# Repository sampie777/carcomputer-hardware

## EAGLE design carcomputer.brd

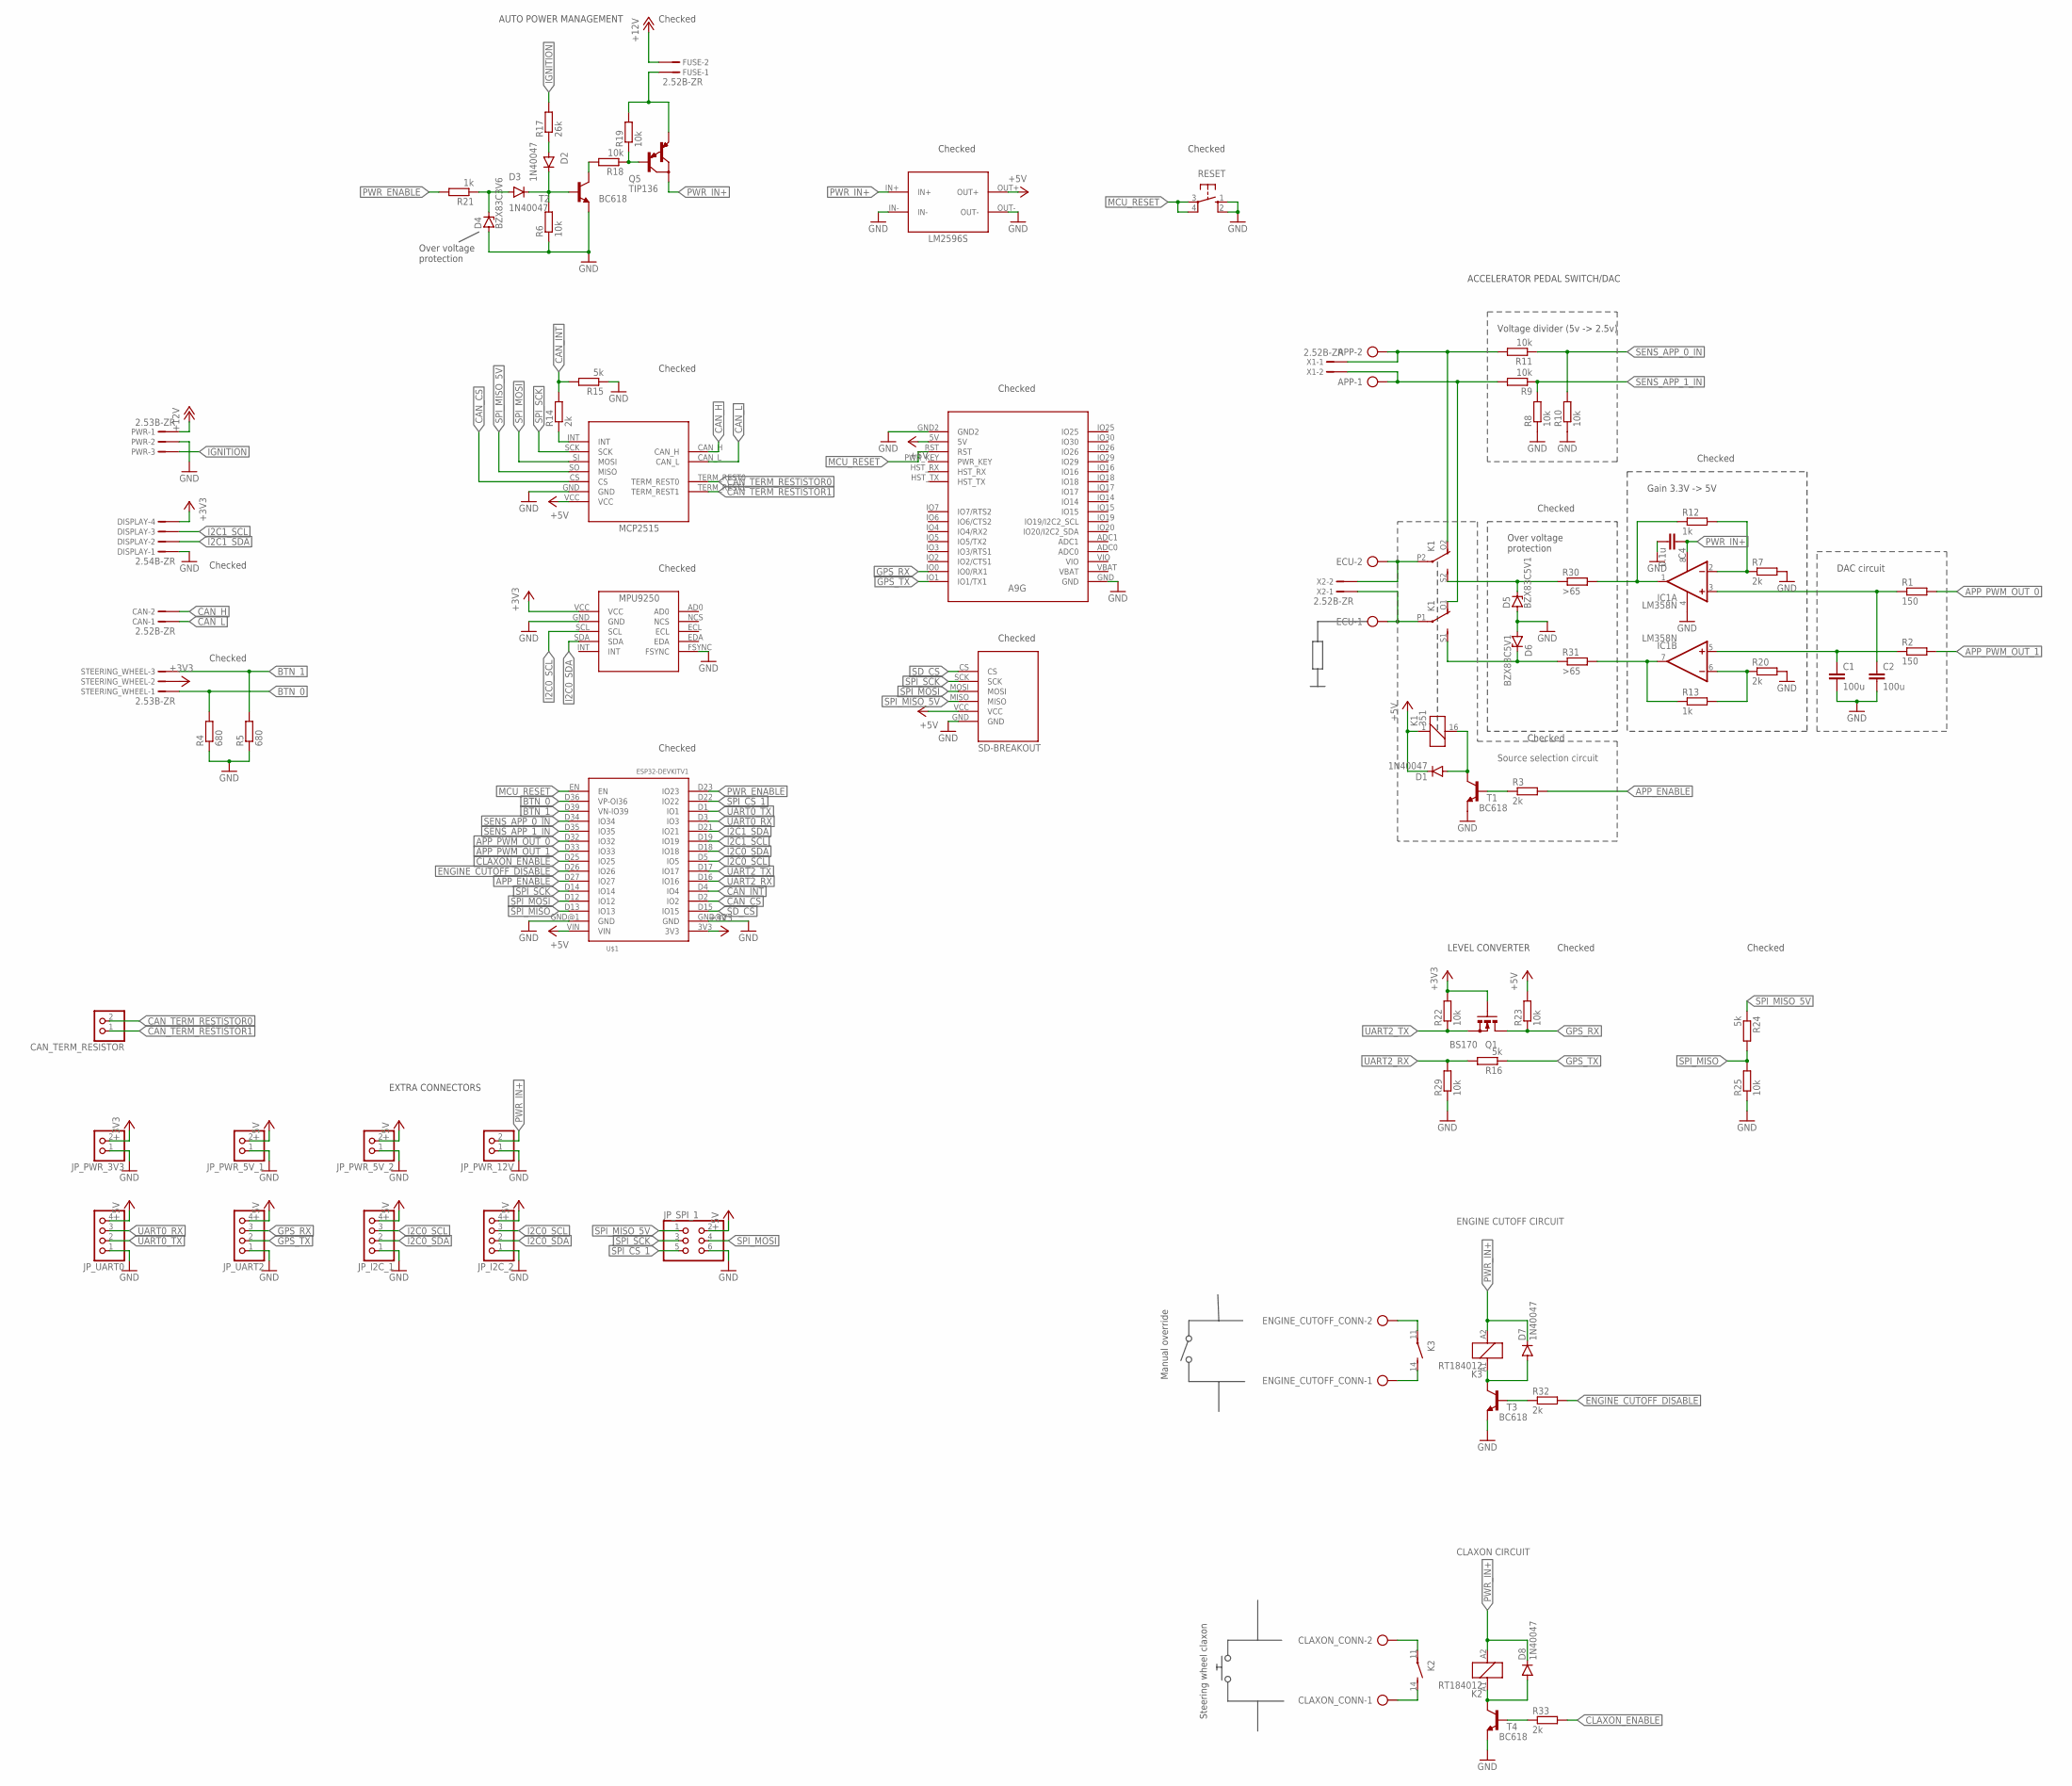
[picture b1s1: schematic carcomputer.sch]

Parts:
APP: AK300/2
C1, C2: 100u; C025-050X050
C4: 0.1u; C025-050X050
CAN: 2.52B-ZR; B2B-ZR2.5
CAN_TERM_RESISTOR: PINHD-1X2; 1X02
CLAXON_CONN: AK300/2
D1, D2, D3, D7, D8: 1N40047; DO41-7.6
D4: BZX83C3V6; DO41Z7.6
D5, D6: BZX83C5V1; DO41Z7.6
DISPLAY: 2.54B-ZR; B4B-ZR2.5
ECU: AK300/2
ENGINE_CUTOFF_CONN: AK300/2
FUSE: 2.52B-ZR; B2B-ZR2.5
IC1: LM358N; DIL08
JP_I2C_1, JP_I2C_2: PINHD-1X4; 1X04
JP_PWR_3V3, JP_PWR_5V_1, JP_PWR_5V_2, JP_PWR_12V: PINHD-1X2; 1X02
JP_SPI_1: PINHD-2X3; 2X03
JP_UART0, JP_UART2: PINHD-1X4; 1X04
K1: 351
K2, K3: RT184012; RT-N/O12A3.5
PWR: 2.53B-ZR; B3B-ZR2.5
Q1: BS170; SOT54E
Q5: TIP136; TO220
R1, R2: 150; 0309/10
R3, R7, R20: 2k; 0207/7
R4, R5: 680; 0207/7
R6, R8, R10, R18, R19, R22, R23, R25, R29: 10k; 0207/7
R9, R11: 10k; 0309/10
R12, R13: 1k; 0207/7
R14, R32, R33: 2k; 0309/10
R15, R16, R24: 5k; 0207/7
R17: 26k; 0207/7
R21: 1k; 0309/10
R30, R31: >65; 0207/7
RESET: 10-XX; B3F-10XX
STEERING_WHEEL: 2.53B-ZR; B3B-ZR2.5
T1, T2, T3, T4: BC618; TO92-EBC
U$1: ESP32DEVKITV1; ESP32-DEVKITV1
U$2: MCP2515_DEVBOARDINVERTED; MCP2515_DEVBOARD_INVERTED
U$3: MPU9250_BREAKOUT
U$4: LM2596S
U$5: HKD-MICRO-SD-BREAKOUTH; HKD-MICRO-SD-BREAKOUT
U$6: A9G
X1, X2: 2.52B-ZR; B2B-ZR2.5

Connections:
+3V3: DISPLAY.4, JP_PWR_3V3.2, Q1.G, R22.2, STEERING_WHEEL.2, U$1.3V3, U$3.VCC
+5V: D1.C, JP_I2C_1.4, JP_I2C_2.4, JP_PWR_5V_1.2, JP_PWR_5V_2.2, JP_SPI_1.2, JP_UART0.4, JP_UART2.4, K1.1, R23.2, U$1.VIN, U$2.VCC, U$4.OUT+, U$5.VCC, U$6.5V
+12V: FUSE.2, PWR.1
APP_0_IN: APP.2, K1.O2 (O), R11.2, X1.1
APP_1_IN: APP.1, K1.O1 (O), R9.2, X1.2
APP_ENABLE: R3.2, U$1.D27 (IO27)
APP_PWM_OUT_0: R1.2, U$1.D32 (IO32)
APP_PWM_OUT_1: R2.2, U$1.D33 (IO33)
BTN_0: R4.2, STEERING_WHEEL.1, U$1.D36 (VP-OI36)
BTN_1: R5.2, STEERING_WHEEL.3, U$1.D39 (VN-IO39)
CAN_CS: U$1.D2 (IO2), U$2.CS
CAN_H: CAN.2, U$2.CAN_H
CAN_INT: R14.2, R15.2, U$1.D4 (IO4)
CAN_L: CAN.1, U$2.CAN_L
CAN_TERM_RESTISTOR0: CAN_TERM_RESISTOR.2, U$2.TERM_REST0
CAN_TERM_RESTISTOR1: CAN_TERM_RESISTOR.1, U$2.TERM_REST1
CLAXON_ENABLE: R33.2, U$1.D25 (IO25)
ENGINE_CUTOFF_DISABLE: R32.2, U$1.D26 (IO26)
GND: C1.2, C2.2, C4.2, D4.A, D5.A, D6.A, DISPLAY.1, IC1.4 (V-), JP_I2C_1.1, JP_I2C_2.1, JP_PWR_3V3.1, JP_PWR_5V_1.1, JP_PWR_5V_2.1, JP_PWR_12V.1, JP_SPI_1.6, JP_UART0.1, JP_UART2.1, PWR.2, R4.1, R5.1, R6.1, R7.2, R8.1, R10.1, R15.1, R20.2, R25.1, R29.1, RESET.1 (S), RESET.2 (S1), T1.E, T2.E, T3.E, T4.E, U$1.GND@1 (GND), U$1.GND@2 (GND), U$2.GND, U$3.FSYNC, U$3.GND, U$4.IN-, U$4.OUT-, U$5.GND, U$6.GND, U$6.GND2
GPS_RX: JP_UART2.3, Q1.D, R23.1, U$6.IO0 (IO0/RX1)
GPS_TX: JP_UART2.2, R16.1, U$6.IO1 (IO1/TX1)
I2C0_SCL: JP_I2C_1.3, JP_I2C_2.3, U$1.D5 (IO5), U$3.SCL
I2C0_SDA: JP_I2C_1.2, JP_I2C_2.2, U$1.D18 (IO18), U$3.SDA
I2C1_SCL: DISPLAY.3, U$1.D19 (IO19)
I2C1_SDA: DISPLAY.2, U$1.D21 (IO21)
IGNITION: PWR.3, R17.2
MCU_RESET: RESET.3, RESET.4 (P1), U$1.EN, U$6.RST
unnamed: D1.A, K1.16 (2), T1.C
unnamed: R3.1, T1.B
unnamed: D6.C, K1.S1 (S), R31.1
unnamed: IC1.1 (OUT), R12.1, R30.2
unnamed: D2.C, D3.C, R6.2, T2.B
unnamed: ECU.2, K1.P2, X2.2
unnamed: ECU.1, K1.P1, X2.1
unnamed: C2.1, IC1.3 (+IN), R1.1
unnamed: C1.1, IC1.5 (+IN), R2.1
unnamed: R14.1, U$2.INT
unnamed: D3.A, D4.C, R21.1
unnamed: D2.A, R17.1
unnamed: IC1.2 (-IN), R7.1, R12.2
unnamed: Q5.1 (B), R18.1, R19.1
unnamed: R18.2, T2.C
unnamed: IC1.6 (-IN), R13.2, R20.1
unnamed: D5.C, K1.S2 (S), R30.1
unnamed: IC1.7 (OUT), R13.1, R31.2
unnamed: ENGINE_CUTOFF_CONN.2, K3.11
unnamed: ENGINE_CUTOFF_CONN.1, K3.14 (S)
unnamed: FUSE.1, Q5.3 (E), R19.2
unnamed: D7.A, K3.A1 (1), T3.C
unnamed: D8.A, K2.A1 (1), T4.C
unnamed: R33.1, T4.B
unnamed: R32.1, T3.B
unnamed: CLAXON_CONN.2, K2.11
unnamed: CLAXON_CONN.1, K2.14 (S)
PWR_ENABLE: R21.2, U$1.D23 (IO23)
PWR_IN+: C4.1, D7.C, D8.C, IC1.8 (V+), JP_PWR_12V.2, K2.A2 (2), K3.A2 (2), Q5.2 (C), U$4.IN+
SD_CS: U$1.D15 (IO15), U$5.CS
SENS_APP_0_IN: R10.2, R11.1, U$1.D34 (IO34)
SENS_APP_1_IN: R8.2, R9.1, U$1.D35 (IO35)
SPI_CS_1: JP_SPI_1.5, U$1.D22 (IO22)
SPI_MISO: R24.2, R25.2, U$1.D13 (IO13)
SPI_MISO_5V: JP_SPI_1.1, R24.1, U$2.SO (MISO), U$5.MISO
SPI_MOSI: JP_SPI_1.4, U$1.D12 (IO12), U$2.SI (MOSI), U$5.MOSI
SPI_SCK: JP_SPI_1.3, U$1.D14 (IO14), U$2.SCK, U$5.SCK
UART0_RX: JP_UART0.3, U$1.D3 (IO3)
UART0_TX: JP_UART0.2, U$1.D1 (IO1)
UART2_RX: R16.2, R29.2, U$1.D16 (IO16)
UART2_TX: Q1.S, R22.1, U$1.D17 (IO17)

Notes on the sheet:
Voltage divider (5v -> 2.5v)
DAC circuit
Source selection circuit
Over voltage protection
AUTO POWER MANAGEMENT
ACCELERATOR PEDAL SWITCH/DAC
EXTRA CONNECTORS
Gain 3.3V -> 5V
Checked
LEVEL CONVERTER
ENGINE CUTOFF CIRCUIT
Manual override
CLAXON CIRCUIT
Steering wheel claxon

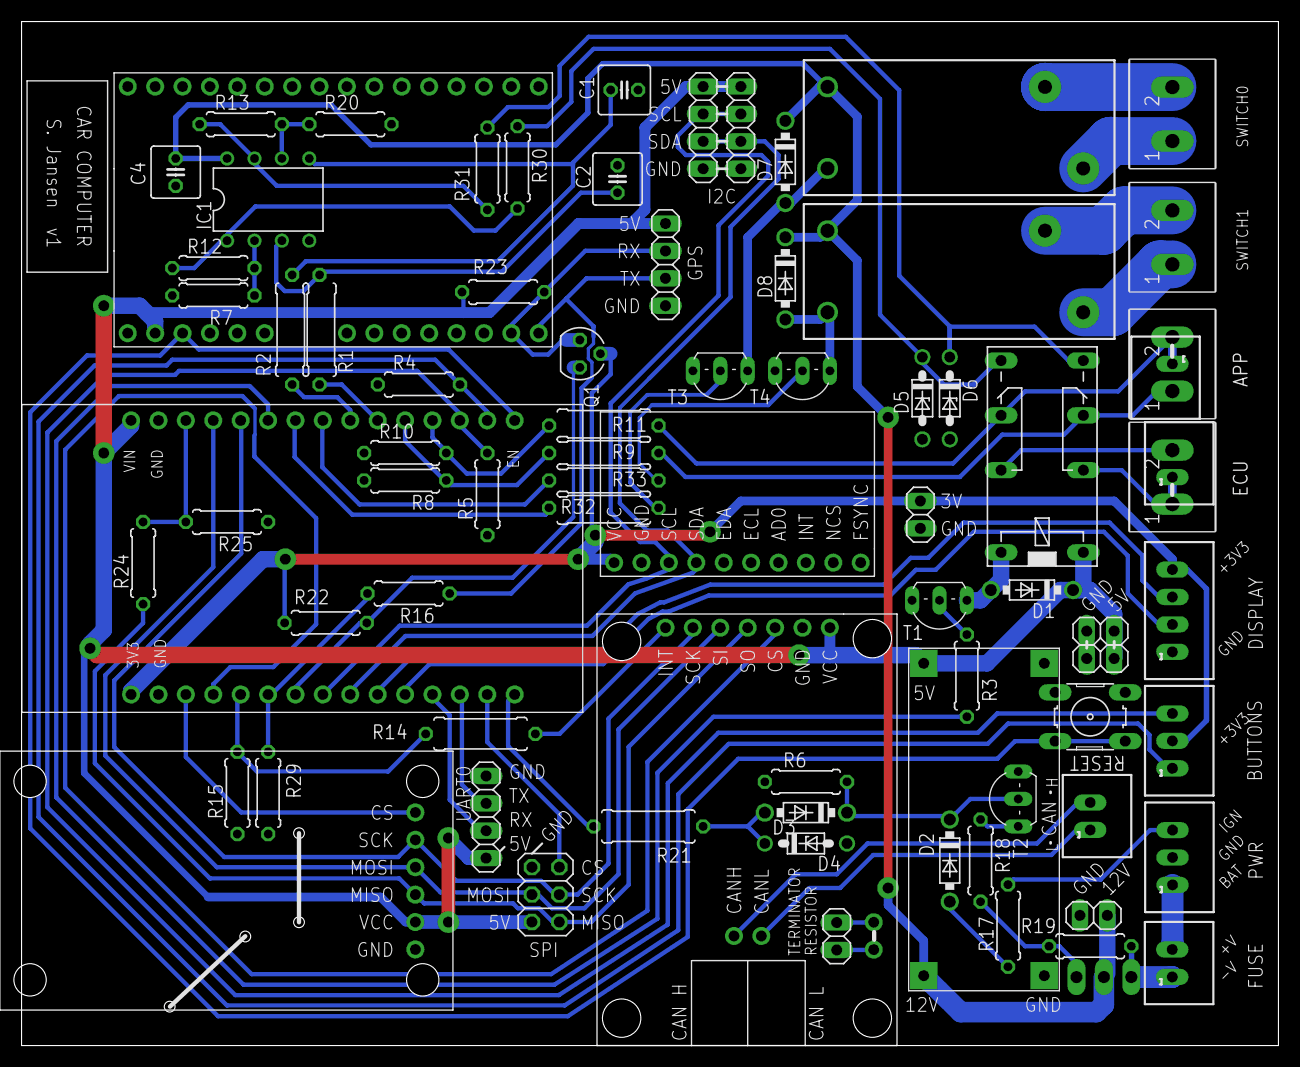
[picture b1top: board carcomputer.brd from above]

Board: 2 copper layers, 116.5 x 94.9 mm, 79 parts (1 on the bottom side), 68 nets.

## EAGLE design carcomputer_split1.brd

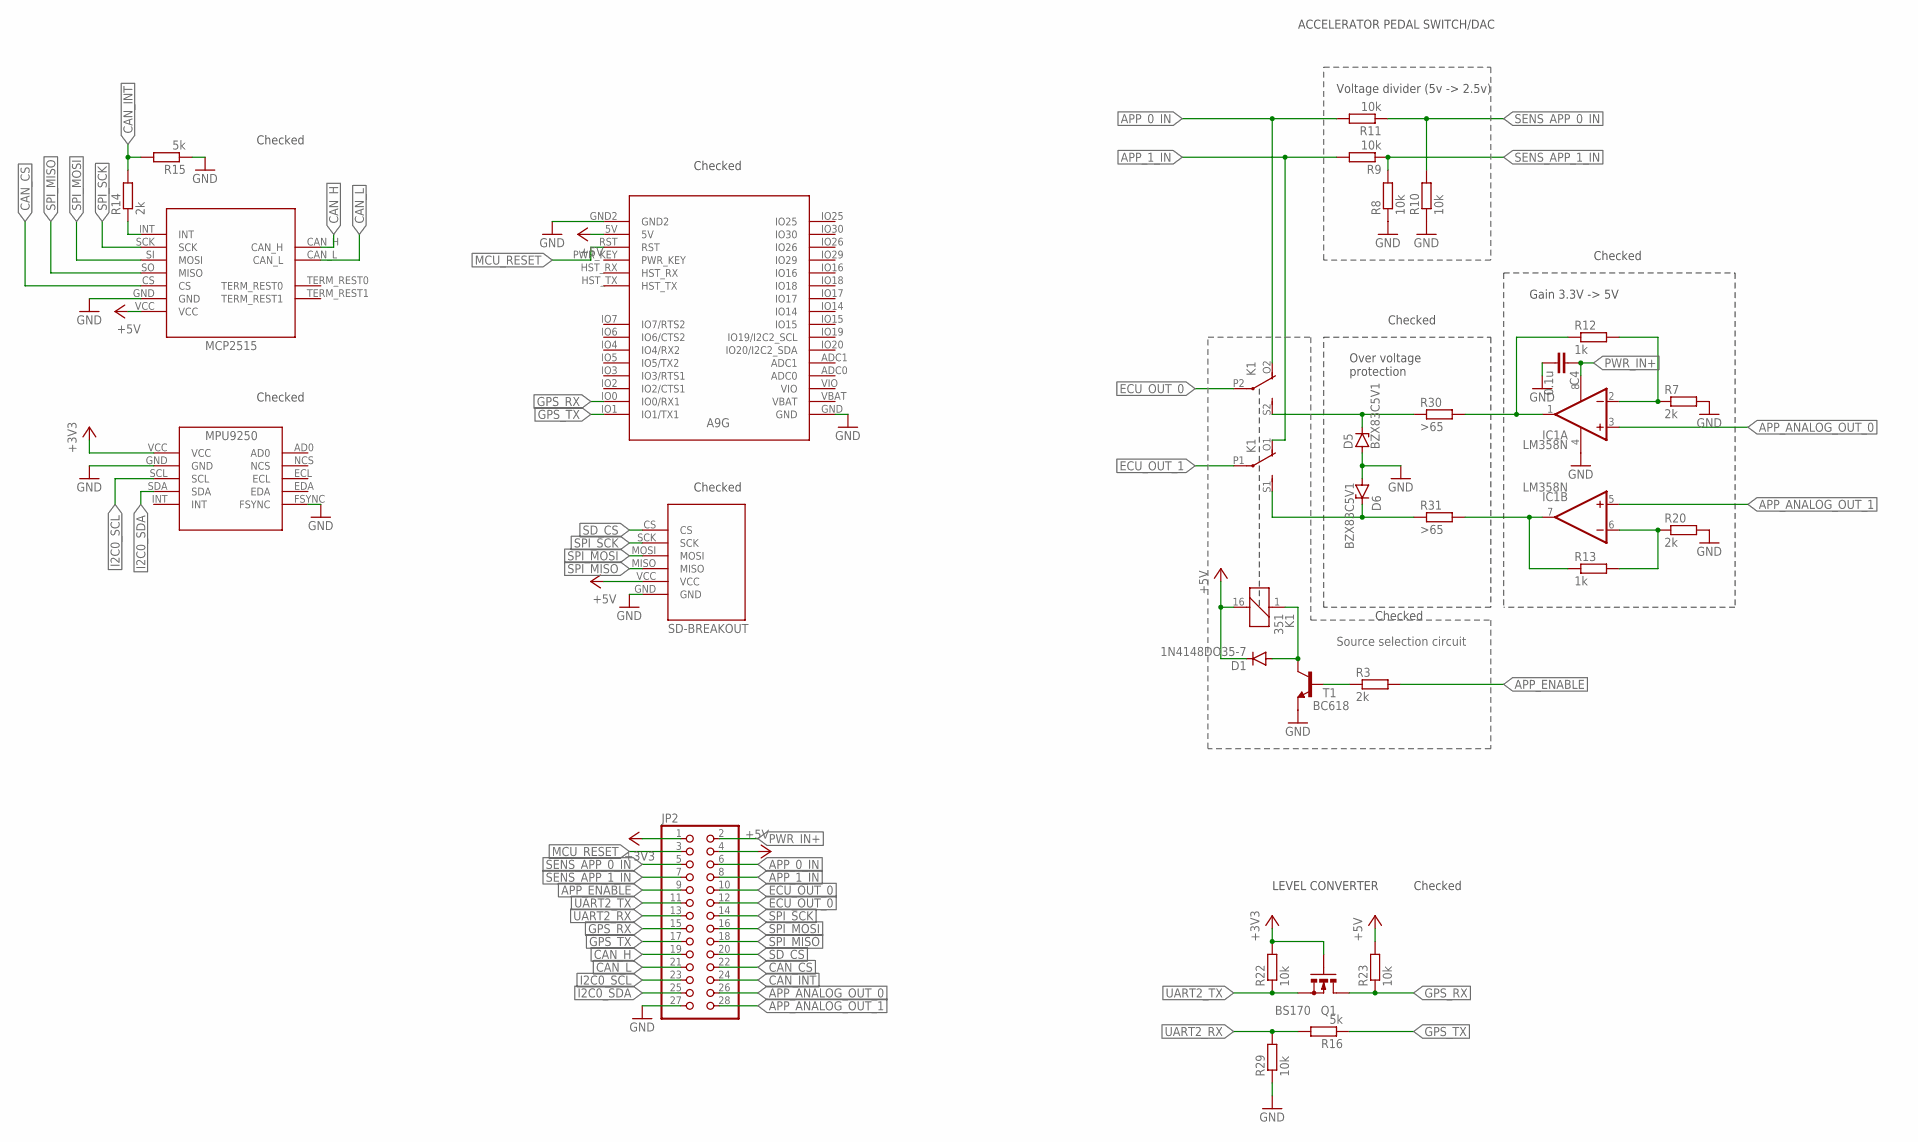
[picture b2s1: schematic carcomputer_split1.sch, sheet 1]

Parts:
C4: 0.1u; C025-050X050
D1: 1N4148DO35-7; DO35-7
D5, D6: BZX83C5V1; DO41Z10
IC1: LM358N; DIL08
JP2: PINHD-2X14; 2X14
K1: 351
Q1: BS170; SOT54E
R3, R7, R14, R20: 2k; 0207/7
R8, R9, R10, R11, R22, R23, R29: 10k; 0207/7
R12, R13: 1k; 0207/7
R15, R16: 5k; 0207/7
R30, R31: >65; 0207/7
T1: BC618; TO92-EBC
U$2: MCP2515_DEVBOARDINVERTED; MCP2515_DEVBOARD_INVERTED
U$3: MPU9250_BREAKOUT
U$5: HKD-MICRO-SD-BREAKOUT
U$6: A9G

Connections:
+3V3: JP2.1, Q1.G, R22.2, U$3.VCC; also elsewhere on the board
+5V: D1.C, JP2.4, K1.16 (2), R23.2, U$2.VCC, U$5.VCC, U$6.5V; also elsewhere on the board
APP_0_IN: JP2.6, K1.O2 (O), R11.2; also elsewhere on the board
APP_1_IN: JP2.8, K1.O1 (O), R9.2; also elsewhere on the board
APP_ANALOG_OUT_0: IC1.3 (+IN), JP2.26; also elsewhere on the board
APP_ANALOG_OUT_1: IC1.5 (+IN), JP2.28; also elsewhere on the board
APP_ENABLE: JP2.9, R3.2; also elsewhere on the board
CAN_CS: JP2.22, U$2.CS; also elsewhere on the board
CAN_H: JP2.19, U$2.CAN_H; also elsewhere on the board
CAN_INT: JP2.24, R14.2, R15.2; also elsewhere on the board
CAN_L: JP2.21, U$2.CAN_L; also elsewhere on the board
ECU_OUT_0: JP2.10, JP2.12, K1.P2; also elsewhere on the board
ECU_OUT_1: K1.P1; also elsewhere on the board
GND: C4.2, D5.A, D6.A, IC1.4 (V-), JP2.27, R7.2, R8.1, R10.1, R15.1, R20.2, R29.1, T1.E, U$2.GND, U$3.FSYNC, U$3.GND, U$5.GND, U$6.GND, U$6.GND2; also elsewhere on the board
GPS_RX: JP2.15, Q1.D, R23.1, U$6.IO0 (IO0/RX1); also elsewhere on the board
GPS_TX: JP2.17, R16.1, U$6.IO1 (IO1/TX1); also elsewhere on the board
I2C0_SCL: JP2.23, U$3.SCL; also elsewhere on the board
I2C0_SDA: JP2.25, U$3.SDA; also elsewhere on the board
MCU_RESET: JP2.3, U$6.RST; also elsewhere on the board
unnamed: D1.A, K1.1, T1.C
unnamed: R3.1, T1.B
unnamed: D6.C, K1.S1 (S), R31.1
unnamed: IC1.1 (OUT), R12.1, R30.2
unnamed: R14.1, U$2.INT
unnamed: IC1.2 (-IN), R7.1, R12.2
unnamed: IC1.6 (-IN), R13.2, R20.1
unnamed: D5.C, K1.S2 (S), R30.1
unnamed: IC1.7 (OUT), R13.1, R31.2
PWR_IN+: C4.1, IC1.8 (V+), JP2.2; also elsewhere on the board
SD_CS: JP2.20, U$5.CS; also elsewhere on the board
SENS_APP_0_IN: JP2.5, R10.2, R11.1; also elsewhere on the board
SENS_APP_1_IN: JP2.7, R8.2, R9.1; also elsewhere on the board
SPI_MISO: JP2.18, U$2.SO (MISO), U$5.MISO; also elsewhere on the board
SPI_MOSI: JP2.16, U$2.SI (MOSI), U$5.MOSI; also elsewhere on the board
SPI_SCK: JP2.14, U$2.SCK, U$5.SCK; also elsewhere on the board
UART2_RX: JP2.13, R16.2, R29.2; also elsewhere on the board
UART2_TX: JP2.11, Q1.S, R22.1; also elsewhere on the board

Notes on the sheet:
Voltage divider (5v -> 2.5v)
Source selection circuit
ACCELERATOR PEDAL SWITCH/DAC
Gain 3.3V -> 5V
Over voltage protection
Checked
LEVEL CONVERTER

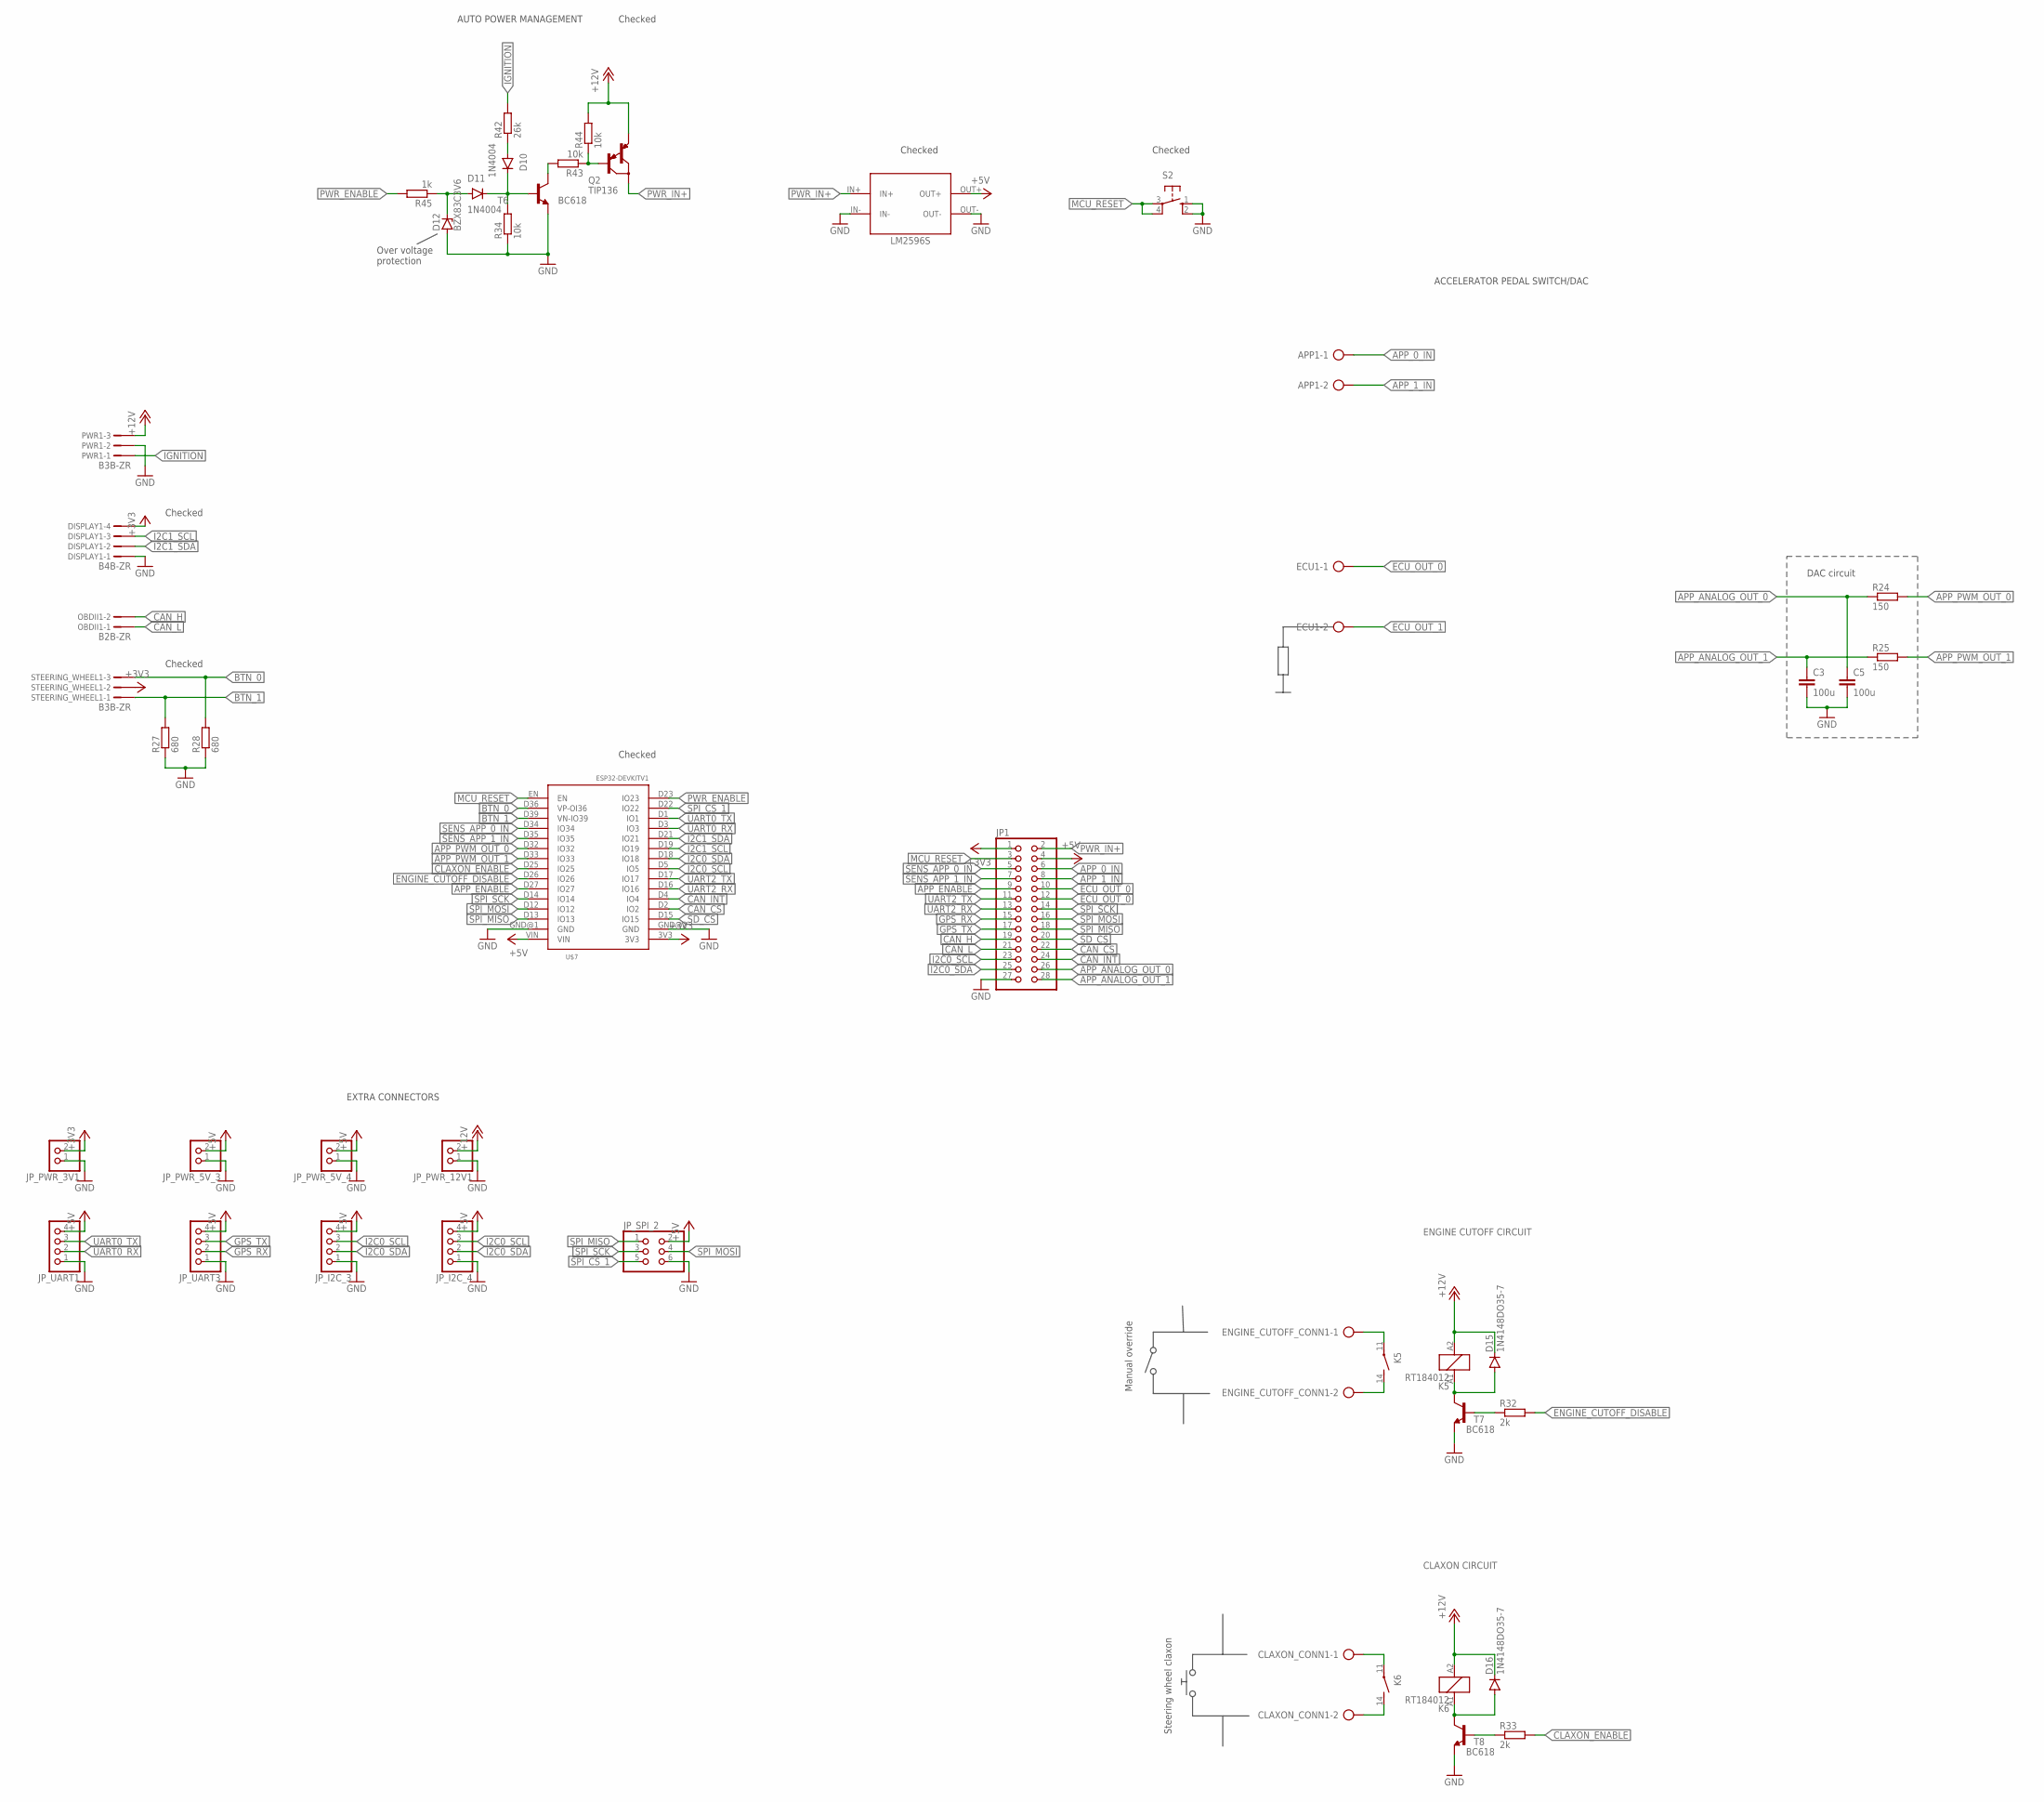
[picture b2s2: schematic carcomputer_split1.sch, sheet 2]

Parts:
APP1: AK300/2
C3, C5: 100u; C025-050X050
CLAXON_CONN1: AK300/2
D10, D11: 1N4004; DO41-10
D12: BZX83C3V6; DO41Z10
D15, D16: 1N4148DO35-7; DO35-7
DISPLAY1: B4B-ZR
ECU1: AK300/2
ENGINE_CUTOFF_CONN1: AK300/2
JP1: PINHD-2X14; 2X14
JP_I2C_3, JP_I2C_4: PINHD-1X4; 1X04
JP_PWR_3V1, JP_PWR_5V_3, JP_PWR_5V_4, JP_PWR_12V1: PINHD-1X2; 1X02
JP_SPI_2: PINHD-2X3; 2X03
JP_UART1, JP_UART3: PINHD-1X4; 1X04
K5, K6: RT184012; RT-N/O12A3.5
OBDII1: B2B-ZR
PWR1: B3B-ZR
Q2: TIP136; TO220
R24, R25: 150; 0207/7
R27, R28: 680; 0207/7
R32, R33: 2k; 0207/7
R34, R43, R44: 10k; 0207/7
R42: 26k; 0207/7
R45: 1k; 0207/7
S2: 10-XX; B3F-10XX
STEERING_WHEEL1: B3B-ZR
T6, T7, T8: BC618; TO92-EBC
U$7: ESP32DEVKITV1; ESP32-DEVKITV1
U$10: LM2596S

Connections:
+3V3: DISPLAY1.4, JP1.1, JP_PWR_3V1.2, STEERING_WHEEL1.2, U$7.3V3; also elsewhere on the board
+5V: JP1.4, JP_I2C_3.4, JP_I2C_4.4, JP_PWR_5V_3.2, JP_PWR_5V_4.2, JP_SPI_2.2, JP_UART1.4, JP_UART3.4, U$7.VIN, U$10.OUT+; also elsewhere on the board
+12V: D15.C, D16.C, JP_PWR_12V1.2, K5.A2 (2), K6.A2 (2), PWR1.3, Q2.3 (E), R44.2
APP_0_IN: APP1.1, JP1.6; also elsewhere on the board
APP_1_IN: APP1.2, JP1.8; also elsewhere on the board
APP_ANALOG_OUT_0: C5.1, JP1.26, R24.1; also elsewhere on the board
APP_ANALOG_OUT_1: C3.1, JP1.28, R25.1; also elsewhere on the board
APP_ENABLE: JP1.9, U$7.D27 (IO27); also elsewhere on the board
APP_PWM_OUT_0: R24.2, U$7.D32 (IO32)
APP_PWM_OUT_1: R25.2, U$7.D33 (IO33)
BTN_0: R28.2, STEERING_WHEEL1.3, U$7.D36 (VP-OI36)
BTN_1: R27.2, STEERING_WHEEL1.1, U$7.D39 (VN-IO39)
CAN_CS: JP1.22, U$7.D2 (IO2); also elsewhere on the board
CAN_H: JP1.19, OBDII1.2; also elsewhere on the board
CAN_INT: JP1.24, U$7.D4 (IO4); also elsewhere on the board
CAN_L: JP1.21, OBDII1.1; also elsewhere on the board
CLAXON_ENABLE: R33.2, U$7.D25 (IO25)
ECU_OUT_0: ECU1.1, JP1.10, JP1.12; also elsewhere on the board
ECU_OUT_1: ECU1.2; also elsewhere on the board
ENGINE_CUTOFF_DISABLE: R32.2, U$7.D26 (IO26)
GND: C3.2, C5.2, D12.A, DISPLAY1.1, JP1.27, JP_I2C_3.1, JP_I2C_4.1, JP_PWR_3V1.1, JP_PWR_5V_3.1, JP_PWR_5V_4.1, JP_PWR_12V1.1, JP_SPI_2.6, JP_UART1.1, JP_UART3.1, PWR1.2, R27.1, R28.1, R34.1, S2.1 (S), S2.2 (S1), T6.E, T7.E, T8.E, U$7.GND@1 (GND), U$7.GND@2 (GND), U$10.IN-, U$10.OUT-; also elsewhere on the board
GPS_RX: JP1.15, JP_UART3.2; also elsewhere on the board
GPS_TX: JP1.17, JP_UART3.3; also elsewhere on the board
I2C0_SCL: JP1.23, JP_I2C_3.3, JP_I2C_4.3, U$7.D5 (IO5); also elsewhere on the board
I2C0_SDA: JP1.25, JP_I2C_3.2, JP_I2C_4.2, U$7.D18 (IO18); also elsewhere on the board
I2C1_SCL: DISPLAY1.3, U$7.D19 (IO19)
I2C1_SDA: DISPLAY1.2, U$7.D21 (IO21)
IGNITION: PWR1.1, R42.2
MCU_RESET: JP1.3, S2.3, S2.4 (P1), U$7.EN; also elsewhere on the board
unnamed: D10.C, D11.C, R34.2, T6.B
unnamed: D10.A, R42.1
unnamed: Q2.1 (B), R43.1, R44.1
unnamed: R43.2, T6.C
unnamed: D11.A, D12.C, R45.1
unnamed: D15.A, K5.A1 (1), T7.C
unnamed: R32.1, T7.B
unnamed: ENGINE_CUTOFF_CONN1.1, K5.11
unnamed: ENGINE_CUTOFF_CONN1.2, K5.14 (S)
unnamed: D16.A, K6.A1 (1), T8.C
unnamed: R33.1, T8.B
unnamed: CLAXON_CONN1.1, K6.11
unnamed: CLAXON_CONN1.2, K6.14 (S)
PWR_ENABLE: R45.2, U$7.D23 (IO23)
PWR_IN+: JP1.2, Q2.2 (C), U$10.IN+; also elsewhere on the board
SD_CS: JP1.20, U$7.D15 (IO15); also elsewhere on the board
SENS_APP_0_IN: JP1.5, U$7.D34 (IO34); also elsewhere on the board
SENS_APP_1_IN: JP1.7, U$7.D35 (IO35); also elsewhere on the board
SPI_CS_1: JP_SPI_2.5, U$7.D22 (IO22)
SPI_MISO: JP1.18, JP_SPI_2.1, U$7.D13 (IO13); also elsewhere on the board
SPI_MOSI: JP1.16, JP_SPI_2.4, U$7.D12 (IO12); also elsewhere on the board
SPI_SCK: JP1.14, JP_SPI_2.3, U$7.D14 (IO14); also elsewhere on the board
UART0_RX: JP_UART1.2, U$7.D3 (IO3)
UART0_TX: JP_UART1.3, U$7.D1 (IO1)
UART2_RX: JP1.13, U$7.D16 (IO16); also elsewhere on the board
UART2_TX: JP1.11, U$7.D17 (IO17); also elsewhere on the board

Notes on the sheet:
DAC circuit
Over voltage protection
AUTO POWER MANAGEMENT
ACCELERATOR PEDAL SWITCH/DAC
EXTRA CONNECTORS
Checked
ENGINE CUTOFF CIRCUIT
Manual override
CLAXON CIRCUIT
Steering wheel claxon

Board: 2 copper layers, 75 parts (0 on the bottom side), 64 nets, no tracks yet.
